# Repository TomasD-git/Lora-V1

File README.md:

# Lora-V1
Very complicated Lora which is mainly for 868mhz but 966mhz would work as well, has a small cell battery to keep track of time for few years, with alot of controls and a screen

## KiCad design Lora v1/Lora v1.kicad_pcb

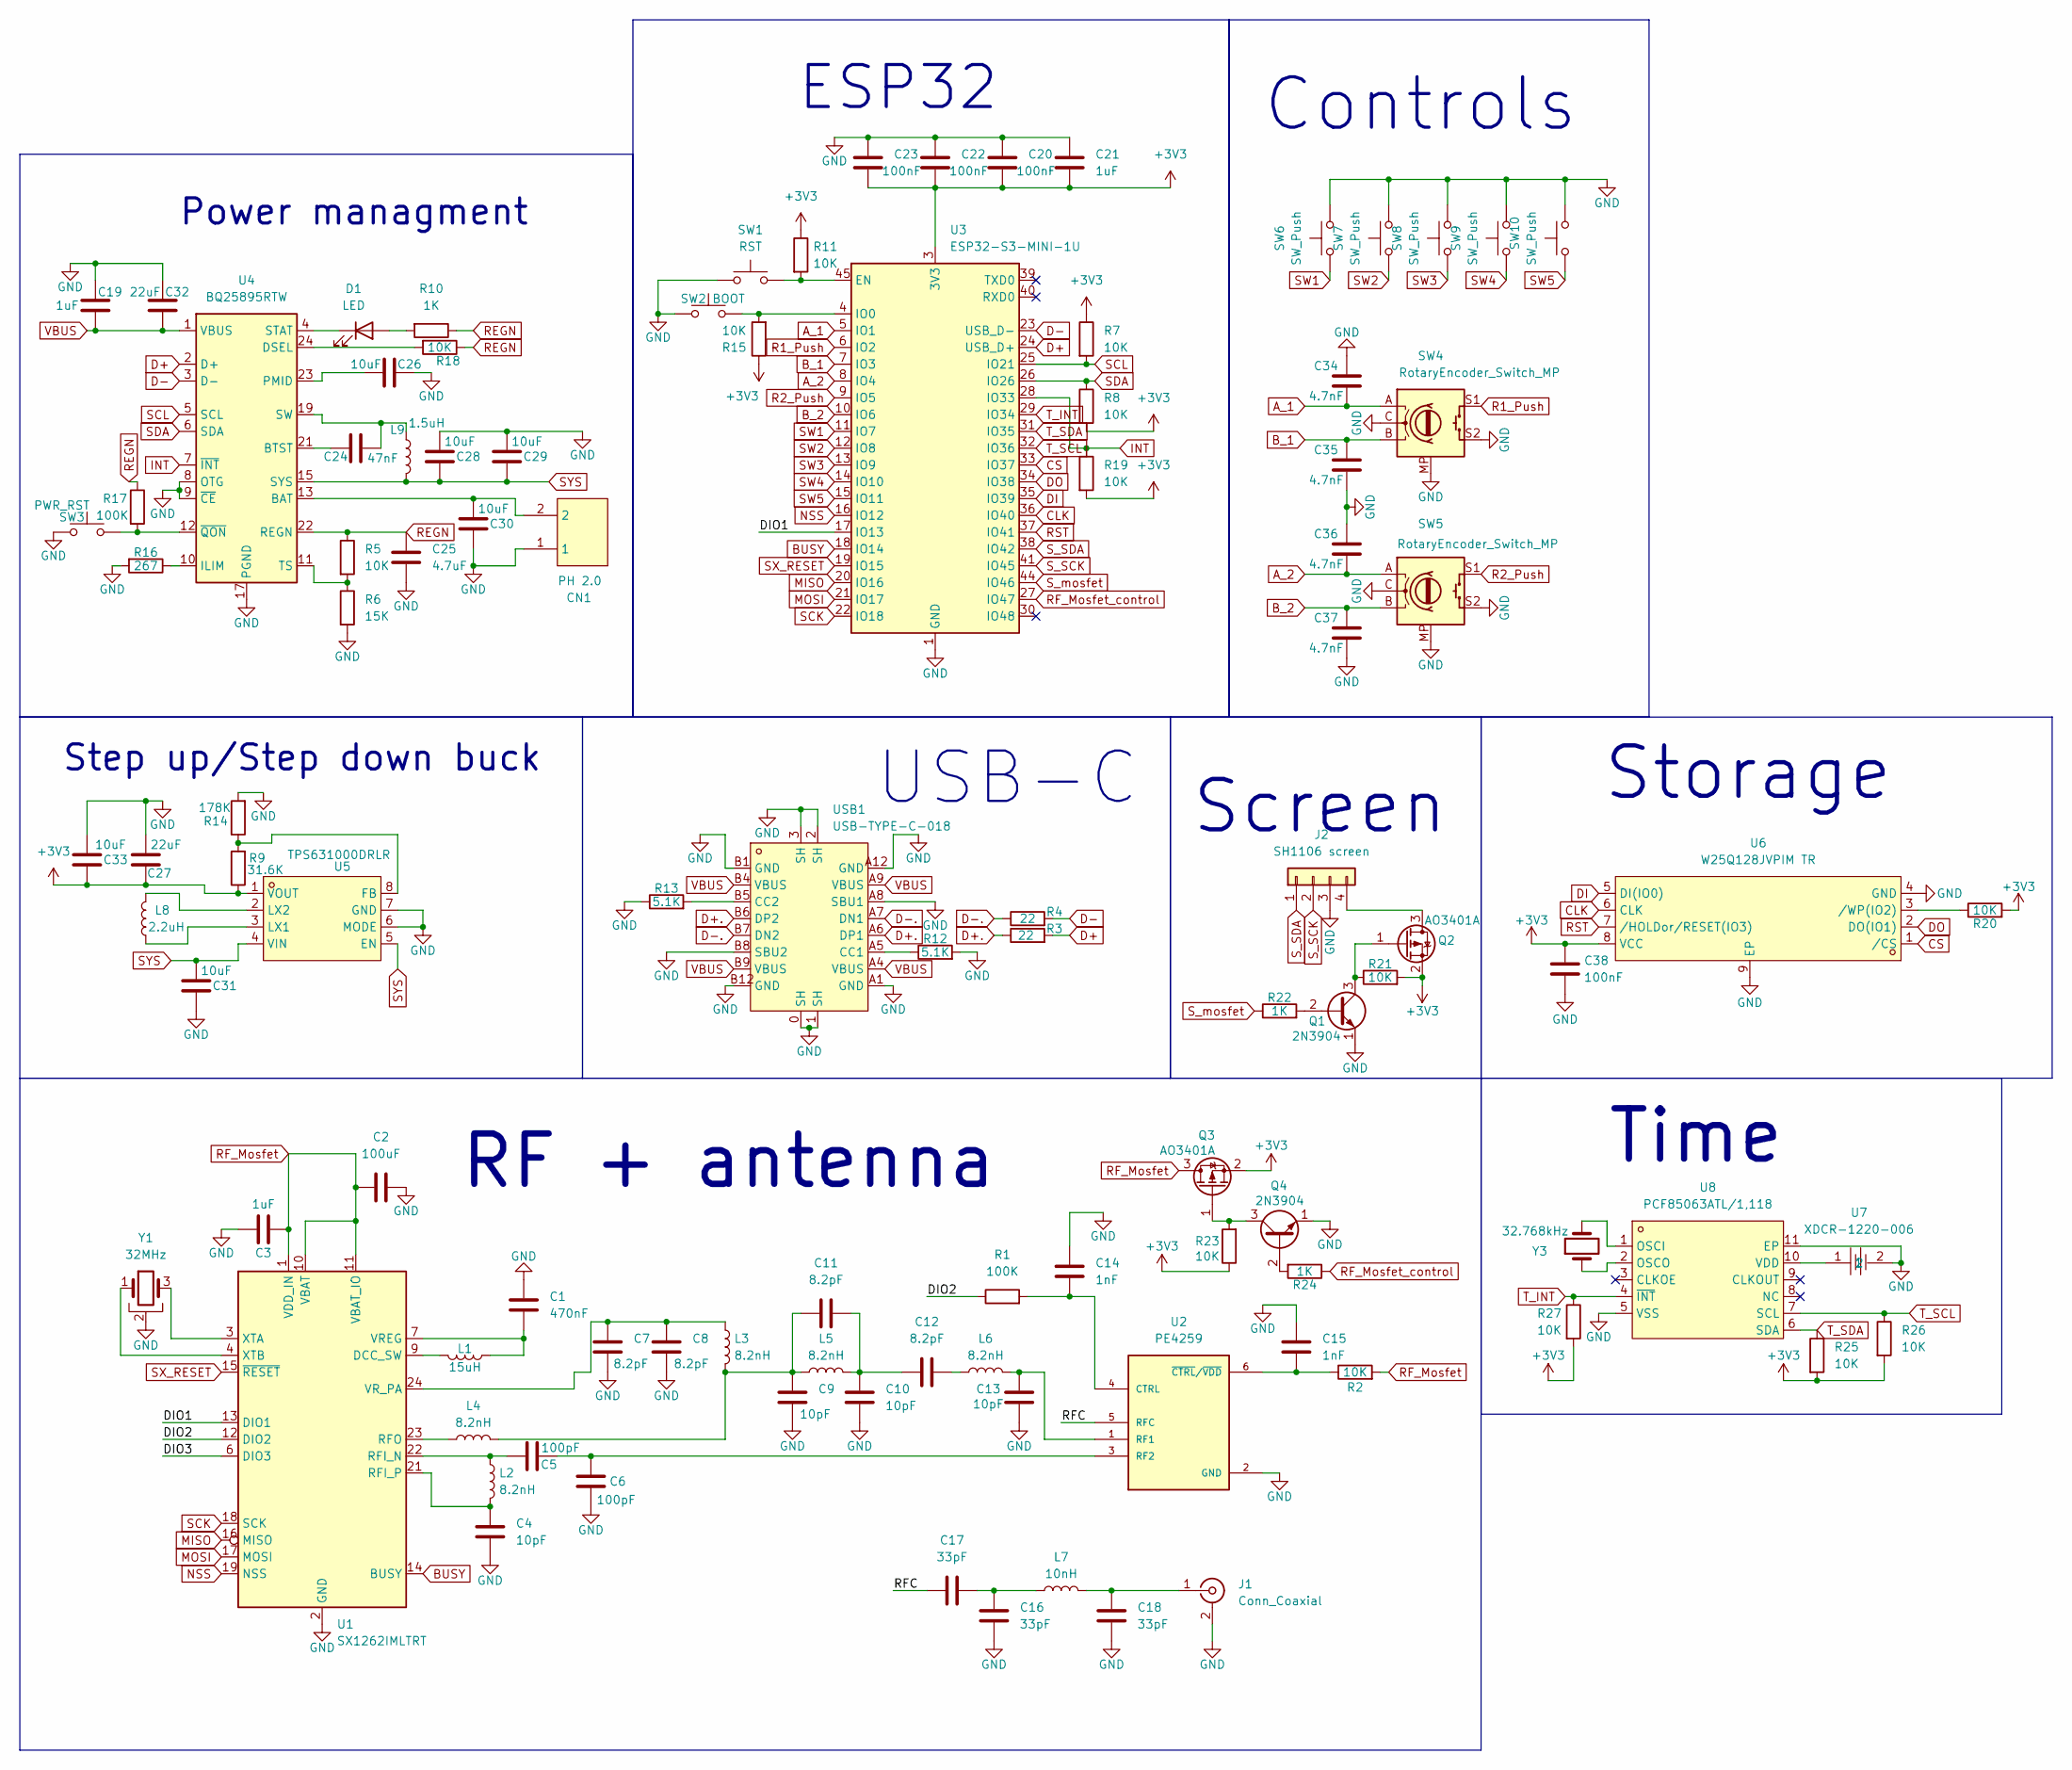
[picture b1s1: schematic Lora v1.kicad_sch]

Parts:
C1: 470nF; C_0402_1005Metric
C2: 100uF; C_1210_3225Metric
C3, C19, C21: 1uF; C_0402_1005Metric
C4, C9, C10, C13: 10pF; C_0402_1005Metric
C5, C6: 100pF; C_0402_1005Metric
C7, C8, C11, C12: 8.2pF; C_0402_1005Metric
C14, C15: 1nF; C_0402_1005Metric
C16, C17, C18: 33pF; C_0402_1005Metric
C20, C22, C23, C38: 100nF; C_0402_1005Metric
C24: 47nF; C_0402_1005Metric
C25: 4.7uF; C_0603_1608Metric
C26, C28, C29, C30, C31, C33: 10uF; C_0603_1608Metric
C27, C32: 22uF; C_0805_2012Metric
C34, C35, C36, C37: 4.7nF; C_0402_1005Metric
CN1: PH 2.0; CONN-TH_B2B-PH-K-S; MPN B2B-PH-K-S(LF)(SN); LCSC Part C131337
D1: LED; LED_0603_1608Metric
J1: Conn_Coaxial; U.FL_Hirose_U.FL-R-SMT-1_Vertical
J2: SH1106 screen; PinHeader_1x04_P2.54mm_Vertical
L1: 15uH; L_0805_2012Metric
L2, L3, L4, L5, L6: 8.2nH; L_0402_1005Metric
L7: 10nH; L_0402_1005Metric
L8: 2.2uH; L_1008_2520Metric
L9: 1.5uH; L_1210_3225Metric
Q1, Q4: 2N3904; TO-92_Inline
Q2, Q3: AO3401A; SOT-23
R1, R17: 100K; R_0402_1005Metric
R2, R5, R7, R8, R11, R15, R18, R19, R20, R21, R23, R25, R26, R27: 10K; R_0402_1005Metric
R3, R4: 22; R_0402_1005Metric
R6: 15K; R_0402_1005Metric
R9: 31.6K; R_0402_1005Metric
R10, R22, R24: 1K; R_0402_1005Metric
R12, R13: 5.1K; R_0402_1005Metric
R14: 178K; R_0402_1005Metric
R16: 267; R_0402_1005Metric
SW1: RST; SW_SPST_PTS645Sx43SMTR92
SW2: BOOT; SW_SPST_PTS645Sx43SMTR92
SW3: PWR_RST; SW_SPST_PTS645Sx43SMTR92
SW4, SW5: RotaryEncoder_Switch_MP; RotaryEncoder_Alps_EC11E-Switch_Vertical_H20mm
SW6, SW7, SW8, SW9, SW10: SW_Push; SW_Cherry_MX_PCB_1.00u
U1: SX1262IMLTRT; QFN-24-1EP_4x4mm_P0.5mm_EP2.6x2.6mm
U2: PE4259; SOT65P215X110-6N
U3: ESP32-S3-MINI-1U; ESP32-S2-MINI-1U
U4: BQ25895RTW; Texas_RTW_WQFN-24-1EP_4x4mm_P0.5mm_EP2.7x2.7mm_ThermalVias
U5: TPS631000DRLR; SOT-583-8_L2.1-W1.2-P0.50-LS1.6-BL; MPN TPS631000DRLR; LCSC Part C5219190
U6: W25Q128JVPIM TR; WSON-8_L6.0-W5.0-P1.27-BL-EP; MPN W25Q128JVPIM TR; LCSC Part C2441427
U7: XDCR-1220-006; BAT-SMD_CR1220-2ZX; MPN XDCR-1220-006; LCSC Part C7498147
U8: PCF85063ATL/1,118; DFN-10_L2.6-W2.6-P0.50-BL-EP; MPN PCF85063ATL/1,118; LCSC Part C404360
USB1: USB-TYPE-C-018; USB-C_SMD-TYPE-C-31-M-12; MPN USB-TYPE-C-018; LCSC Part C2927038
Y1: 32MHz; Crystal_SMD_3225-4Pin_3.2x2.5mm
Y3: 32.768kHz; Crystal_SMD_3215-2Pin_3.2x1.5mm

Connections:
+3V3: C20.2, C21.2, C22.2, C23.2, C27.1, C33.1, C38.1, Q2.2 (S), Q3.2 (S), R7.1, R8.2, R9.1, R11.1, R15.1, R19.2, R20.2, R21.2, R23.1, R25.2, R26.2, R27.2, U3.3 (3V3), U5.1 (VOUT), U6.8 (VCC)
/DIO1: U1.13 (DIO1), U3.17 (IO13)
/DIO2: R1.1, U1.12 (DIO2)
/DIO3: U1.6 (DIO3)
/RFC: C17.1, U2.5 (RFC)
A_1: C34.1, SW4.A, U3.5 (IO1)
A_2: C36.1, SW5.A, U3.8 (IO4)
BUSY: U1.14 (BUSY), U3.18 (IO14)
B_1: C35.2, SW4.B, U3.7 (IO3)
B_2: C37.2, SW5.B, U3.10 (IO6)
CLK: U3.36 (IO40), U6.6 (CLK)
CS: U3.33 (IO37), U6.1 (/CS)
D+: R3.2, U3.24 (USB_D+), U4.2 (D+)
D+.: R3.1, USB1.A6 (DP1), USB1.B6 (DP2)
D-: R4.2, U3.23 (USB_D-), U4.3 (D-)
D-.: R4.1, USB1.A7 (DN1), USB1.B7 (DN2)
DI: U3.35 (IO39), U6.5 (DI(IO0))
DO: U3.34 (IO38), U6.2 (DO(IO1))
GND: C1.1, C2.2, C3.1, C4.2, C6.1, C7.2, C8.2, C9.2, C10.2, C13.2, C14.1, C15.1, C16.2, C18.2, C19.1, C20.1, C21.1, C22.1, C23.1, C25.2, C26.2, C27.2, C28.2, C29.2, C30.1, C31.1, C32.1, C33.2, C34.2, C35.1, C36.2, C37.1, C38.2, CN1.1, J1.2 (Ext), J2.3, Q1.1 (E), Q4.1 (E), R6.2, R12.2, R13.1, R14.2, R16.2, SW1.1, SW2.1, SW3.1, SW4.C, SW4.MP, SW4.S2, SW5.C, SW5.MP, SW5.S2, SW6.2, SW7.2, SW8.2, SW9.2, SW10.2, U1.2 (GND), U1.5 (GND), U1.8 (GND), U1.20 (GND), U1.25 (GND), U2.2 (GND), U3.1 (GND), U3.2 (GND), U3.42 (GND), U3.43 (GND), U3.46 (GND), U3.47 (GND), U3.48 (GND), U3.49 (GND), U3.50 (GND), U3.51 (GND), U3.52 (GND), U3.53 (GND), U3.54 (GND), U3.55 (GND), U3.56 (GND), U3.57 (GND), U3.58 (GND), U3.59 (GND), U3.60 (GND), U3.61 (GND), U3.62 (GND), U3.63 (GND), U3.64 (GND), U3.65 (GND), U4.8 (OTG), U4.9 (~CE), U4.17 (PGND), U4.18 (PGND), U4.25 (PGND), U5.6 (MODE), U5.7 (GND), U6.4 (GND), U6.9 (EP), U7.2, U8.5 (VSS), U8.11 (EP), USB1.0 (SH), USB1.1 (SH), USB1.2 (SH), USB1.3 (SH), USB1.A1 (GND), USB1.A8 (SBU1), USB1.A12 (GND), USB1.B1 (GND), USB1.B8 (SBU2), USB1.B12 (GND), Y1.2
INT: R19.1, U3.28 (IO33), U4.7 (~INT)
MISO: U1.16 (MISO), U3.20 (IO16)
MOSI: U1.17 (MOSI), U3.21 (IO17)
NSS: U1.19 (NSS), U3.16 (IO12)
unnamed: C10.1, C11.2, C12.1, L5.2
unnamed: C9.1, C11.1, L3.2, L4.2, L5.1
unnamed: C12.2, L6.1
unnamed: C16.1, C17.2, L7.1
unnamed: C24.1, L9.1, U4.19 (SW), U4.20 (SW)
unnamed: C30.2, CN1.2, U4.13 (BAT), U4.14 (BAT)
unnamed: D1.2 (A), R10.2
unnamed: D1.1 (K), U4.4 (STAT)
unnamed: C18.1, J1.1 (In), L7.2
unnamed: J2.4, Q2.3 (D)
unnamed: Q1.2 (B), R22.2
unnamed: Q1.3 (C), Q2.1 (G), R21.1
unnamed: Q3.1 (G), Q4.3 (C), R23.2
unnamed: Q4.2 (B), R24.2
unnamed: L1.2, U1.9 (DCC_SW)
unnamed: C5.1, L2.1, U1.22 (RFI_N)
unnamed: C4.1, L2.2, U1.21 (RFI_P)
unnamed: L4.1, U1.23 (RFO)
unnamed: C1.2, L1.1, U1.7 (VREG)
unnamed: C7.1, C8.1, L3.1, U1.24 (VR_PA)
unnamed: U1.3 (XTA), Y1.3
unnamed: U1.4 (XTB), Y1.1
unnamed: C14.2, R1.2, U2.4 (CTRL)
unnamed: C13.1, L6.2, U2.1 (RF1)
unnamed: C5.2, C6.2, U2.3 (RF2)
unnamed: C15.2, R2.1, U2.6 (~CTRL/~VDD)
unnamed: R11.2, SW1.2, U3.45 (EN)
unnamed: R15.2, SW2.2, U3.4 (IO0)
unnamed: C24.2, U4.21 (BTST)
unnamed: R18.2, U4.24 (DSEL)
unnamed: R16.1, U4.10 (ILIM)
unnamed: C26.1, U4.23 (PMID)
unnamed: R5.2, R6.1, U4.11 (TS)
unnamed: R17.2, SW3.2, U4.12 (~QON)
unnamed: R9.2, R14.1, U5.8 (FB)
unnamed: L8.1, U5.3 (LX1)
unnamed: L8.2, U5.2 (LX2)
unnamed: R20.1, U6.3 (/WP(IO2))
unnamed: U8.1 (OSCI), Y3.2
unnamed: U8.2 (OSCO), Y3.1
unnamed: U7.1, U8.10 (VDD)
unnamed: R12.1, USB1.A5 (CC1)
unnamed: R13.2, USB1.B5 (CC2)
R1_Push: SW4.S1, U3.6 (IO2)
R2_Push: SW5.S1, U3.9 (IO5)
REGN: C25.1, R5.1, R10.1, R17.1, R18.1, U4.22 (REGN)
RF_Mosfet: C2.1, C3.2, Q3.3 (D), R2.2, U1.1 (VDD_IN), U1.10 (VBAT), U1.11 (VBAT_IO)
RF_Mosfet_control: R24.1, U3.27 (IO47)
RST: U3.37 (IO41), U6.7 (/HOLDor/RESET(IO3))
SCK: U1.18 (SCK), U3.22 (IO18)
SCL: R7.2, U3.25 (IO21), U4.5 (SCL)
SDA: R8.1, U3.26 (IO26), U4.6 (SDA)
SW1: SW6.1, U3.11 (IO7)
SW2: SW7.1, U3.12 (IO8)
SW3: SW8.1, U3.13 (IO9)
SW4: SW9.1, U3.14 (IO10)
SW5: SW10.1, U3.15 (IO11)
SX_RESET: U1.15 (~RESET), U3.19 (IO15)
SYS: C28.1, C29.1, C31.2, L9.2, U4.15 (SYS), U4.16 (SYS), U5.4 (VIN), U5.5 (EN)
S_SCK: J2.2, U3.41 (IO45)
S_SDA: J2.1, U3.38 (IO42)
S_mosfet: R22.1, U3.44 (IO46)
T_INT: R27.1, U3.29 (IO34), U8.4 (~INT)
T_SCL: R26.1, U3.32 (IO36), U8.7 (SCL)
T_SDA: R25.1, U3.31 (IO35), U8.6 (SDA)
VBUS: C19.2, C32.2, U4.1 (VBUS), USB1.A4 (VBUS), USB1.A9 (VBUS), USB1.B4 (VBUS), USB1.B9 (VBUS)

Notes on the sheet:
Power managment
Step up/Step down buck
Time
Storage
Controls
ESP32
RF + antenna
USB-C
Screen

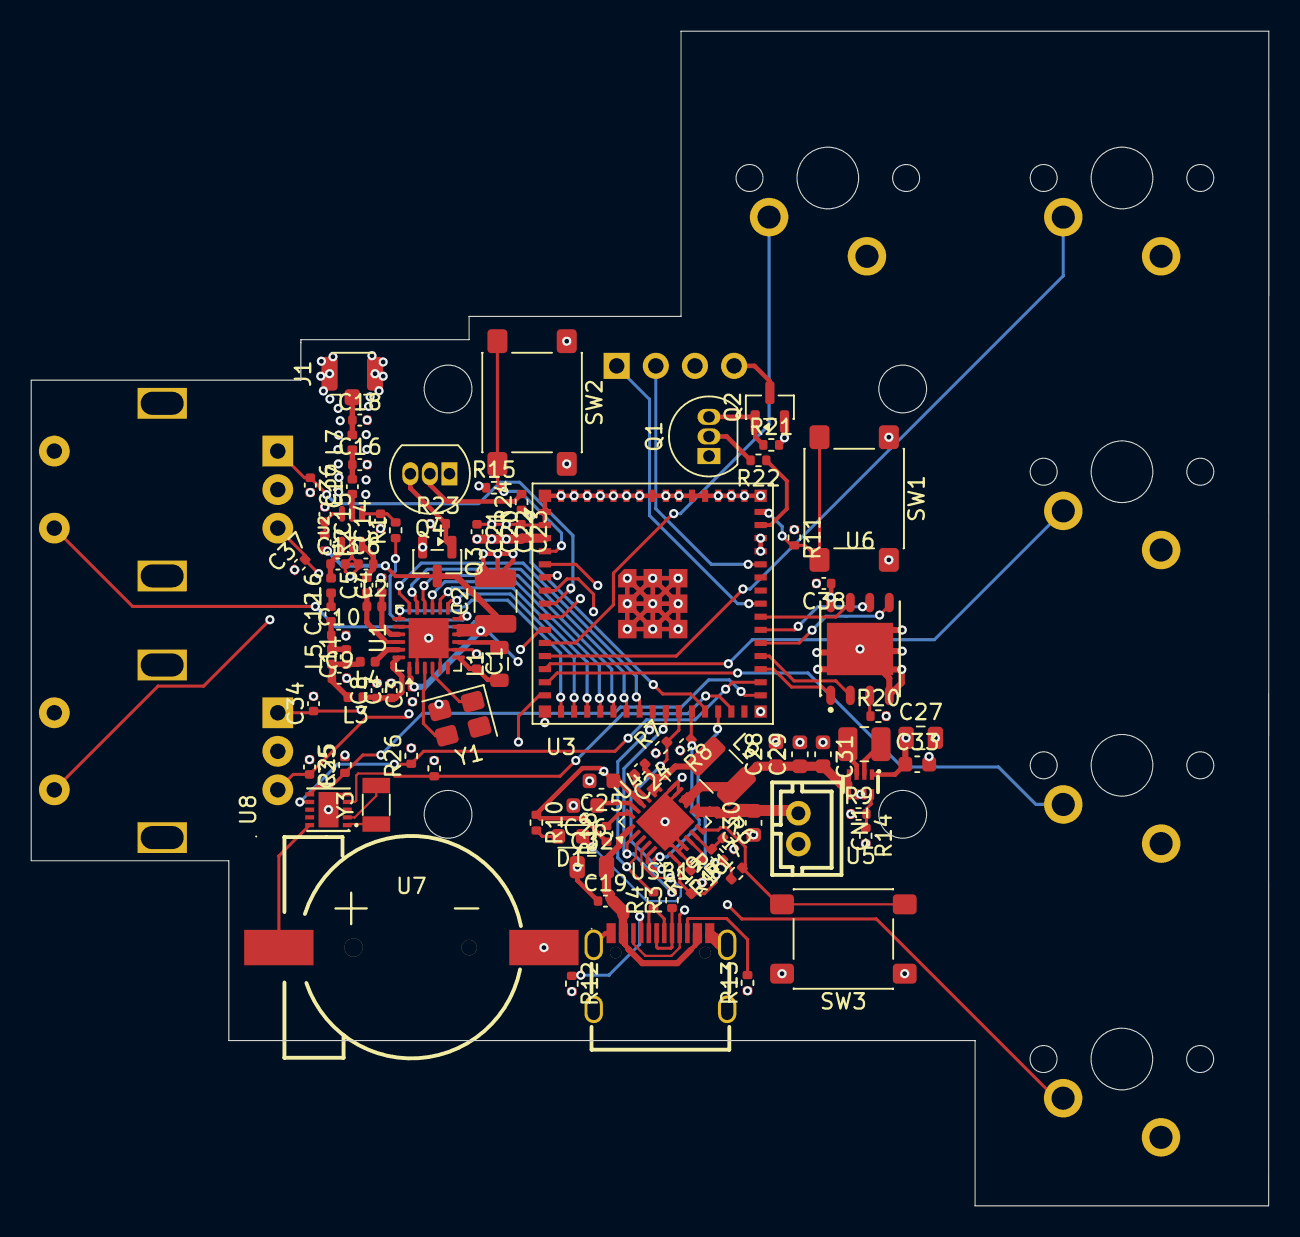
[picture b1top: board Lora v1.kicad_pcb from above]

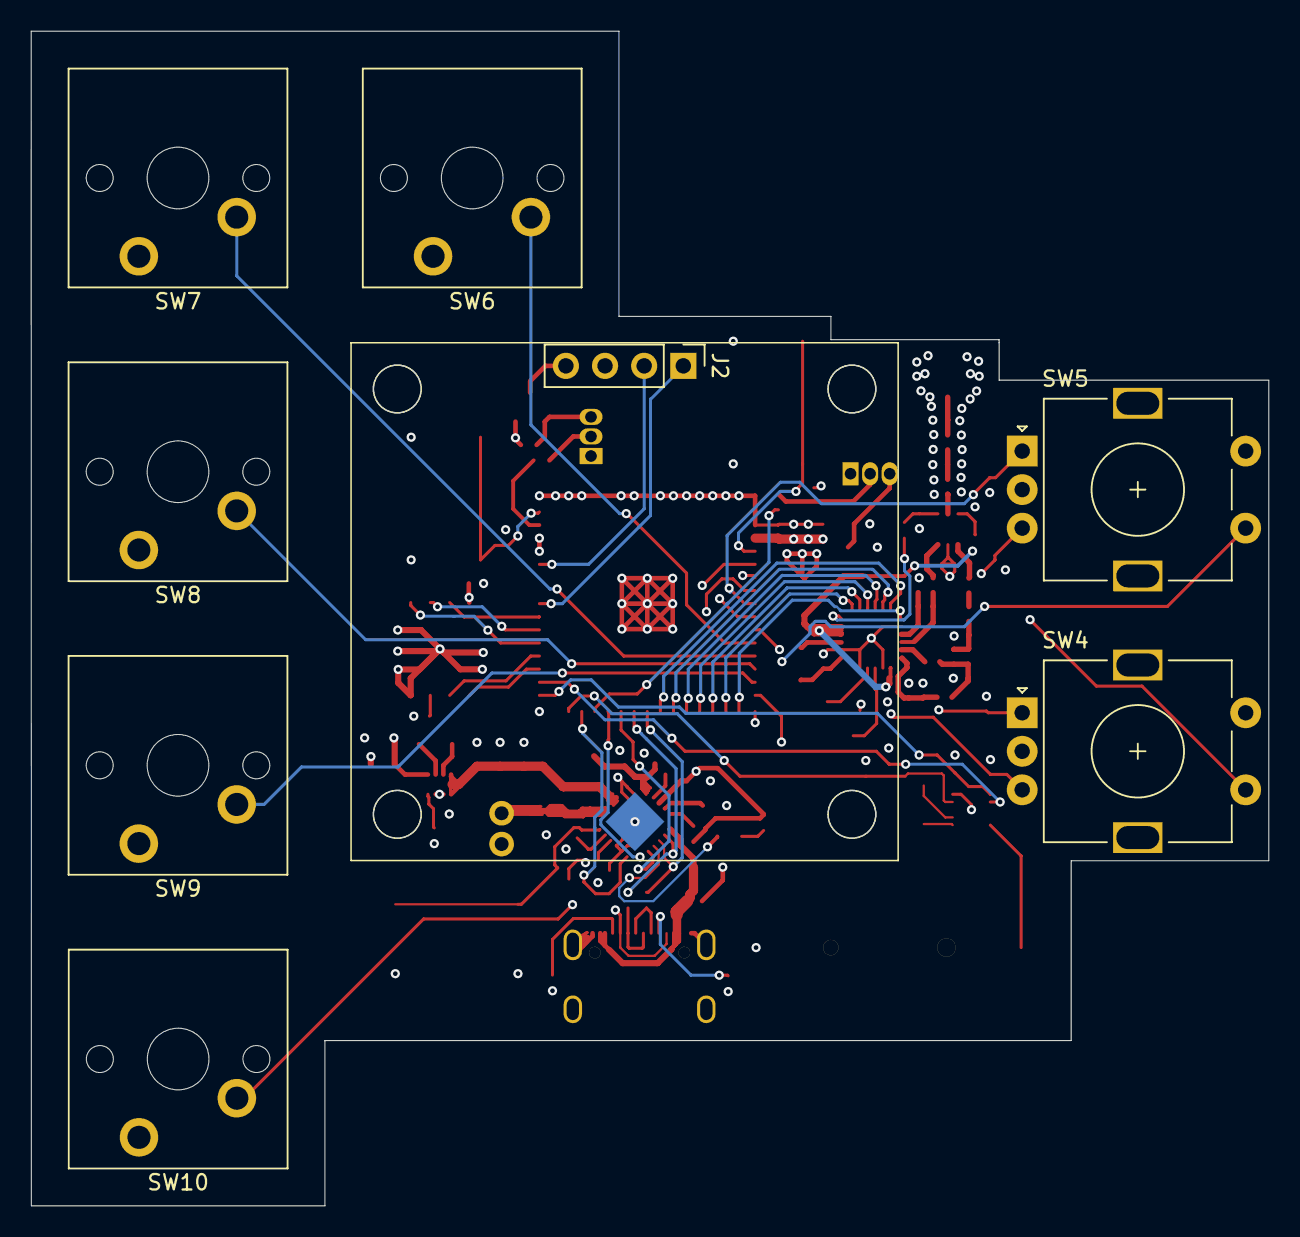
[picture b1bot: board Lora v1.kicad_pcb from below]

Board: 4 copper layers, 80.3 x 76.2 mm, 103 parts (8 on the bottom side), 88 nets.

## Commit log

2026-05-27 added main files
2026-05-27 Add images to README for better visualization
    Added images to enhance the README documentation.
2026-05-27 added firmware
